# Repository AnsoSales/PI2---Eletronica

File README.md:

# PI2 - Eletrônica 

Repositório criado para armazenar os códigos utilizados para o microcontrolador principal do projeto de PI2 e para o arduino.

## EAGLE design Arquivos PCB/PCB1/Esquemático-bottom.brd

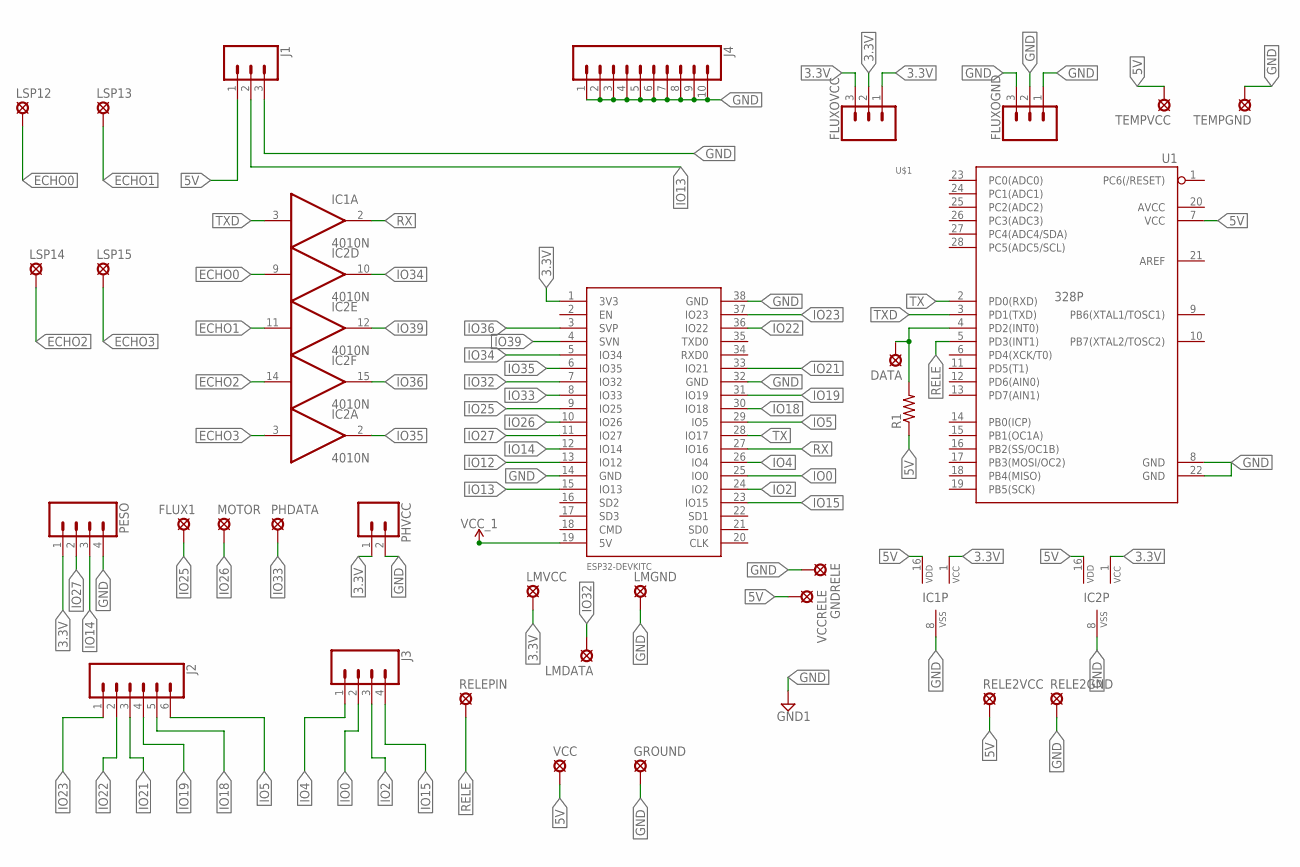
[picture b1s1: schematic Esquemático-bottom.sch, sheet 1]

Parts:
DATA: SE14
FLUX1: SE14
FLUXOGND: CONN_03; 1X03
FLUXOVCC: CONN_03; 1X03
GNDRELE: SE14
GROUND: SE14
IC1, IC2: 4010N; DIL16
J1: CONN_03; 1X03
J2: CONN_06SILK_FEMALE_PTH; 1X06
J3: CONN_04; 1X04
J4: CONN_10"; 1X10
LMDATA: SE14
LMGND: SE14
LMVCC: SE14
LSP12, LSP13, LSP14, LSP15: SE14
MOTOR: SE14
PESO: CONN_04; 1X04
PHDATA: SE14
PHVCC: CONN_02; 1X02
R1: R-US_0207/12; 0207/12
RELE2GND, RELE2VCC: SE14
RELEPIN: SE14
TEMPGND: SE14
TEMPVCC: SE14
U1: 328P; DIP28
U$1: ESP32DEVKITC; ESP32-DEVKITC
VCC: SE14
VCCRELE: SE14

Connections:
3.3V: FLUXOVCC.1, FLUXOVCC.2, FLUXOVCC.3, IC1.1 (VCC), IC2.1 (VCC), LMVCC.MP, PESO.1, PHVCC.1, U$1.1 (3V3)
5V: IC1.16 (VDD), IC2.16 (VDD), J1.1, R1.1, RELE2VCC.MP, TEMPVCC.MP, U1.7 (VCC), U$1.19 (5V), VCC.MP, VCCRELE.MP
ECHO0: IC2.9 (I), LSP12.MP
ECHO1: IC2.11 (I), LSP13.MP
ECHO2: IC2.14 (I), LSP14.MP
ECHO3: IC2.3 (I), LSP15.MP
GND: FLUXOGND.1, FLUXOGND.2, FLUXOGND.3, GNDRELE.MP, GROUND.MP, IC1.8 (VSS), IC2.8 (VSS), J1.3, J4.1, J4.2, J4.3, J4.4, J4.5, J4.6, J4.7, J4.8, J4.9, J4.10, LMGND.MP, PESO.4, PHVCC.2, RELE2GND.MP, TEMPGND.MP, U1.8 (GND), U1.22 (GND), U$1.14 (GND), U$1.32 (GND), U$1.38 (GND)
IO0: J3.2, U$1.25 (IO0)
IO2: J3.3, U$1.24 (IO2)
IO4: J3.1, U$1.26 (IO4)
IO5: J2.6, U$1.29 (IO5)
IO12: U$1.13 (IO12)
IO13: J1.2, U$1.15 (IO13)
IO14: PESO.3, U$1.12 (IO14)
IO15: J3.4, U$1.23 (IO15)
IO18: J2.5, U$1.30 (IO18)
IO19: J2.4, U$1.31 (IO19)
IO21: J2.3, U$1.33 (IO21)
IO22: J2.2, U$1.36 (IO22)
IO23: J2.1, U$1.37 (IO23)
IO25: FLUX1.MP, U$1.9 (IO25)
IO26: MOTOR.MP, U$1.10 (IO26)
IO27: PESO.2, U$1.11 (IO27)
IO32: LMDATA.MP, U$1.7 (IO32)
IO33: PHDATA.MP, U$1.8 (IO33)
IO34: IC2.10 (O), U$1.5 (IO34)
IO35: IC2.2 (O), U$1.6 (IO35)
IO36: IC2.15 (O), U$1.3 (SVP)
IO39: IC2.12 (O), U$1.4 (SVN)
unnamed: DATA.MP, R1.2, U1.4 (PD2(INT0))
RELE: RELEPIN.MP, U1.5 (PD3(INT1))
RX: IC1.2 (O), U$1.27 (IO16)
TX: U1.2 (PD0(RXD)), U$1.28 (IO17)
TXD: IC1.3 (I), U1.3 (PD1(TXD))

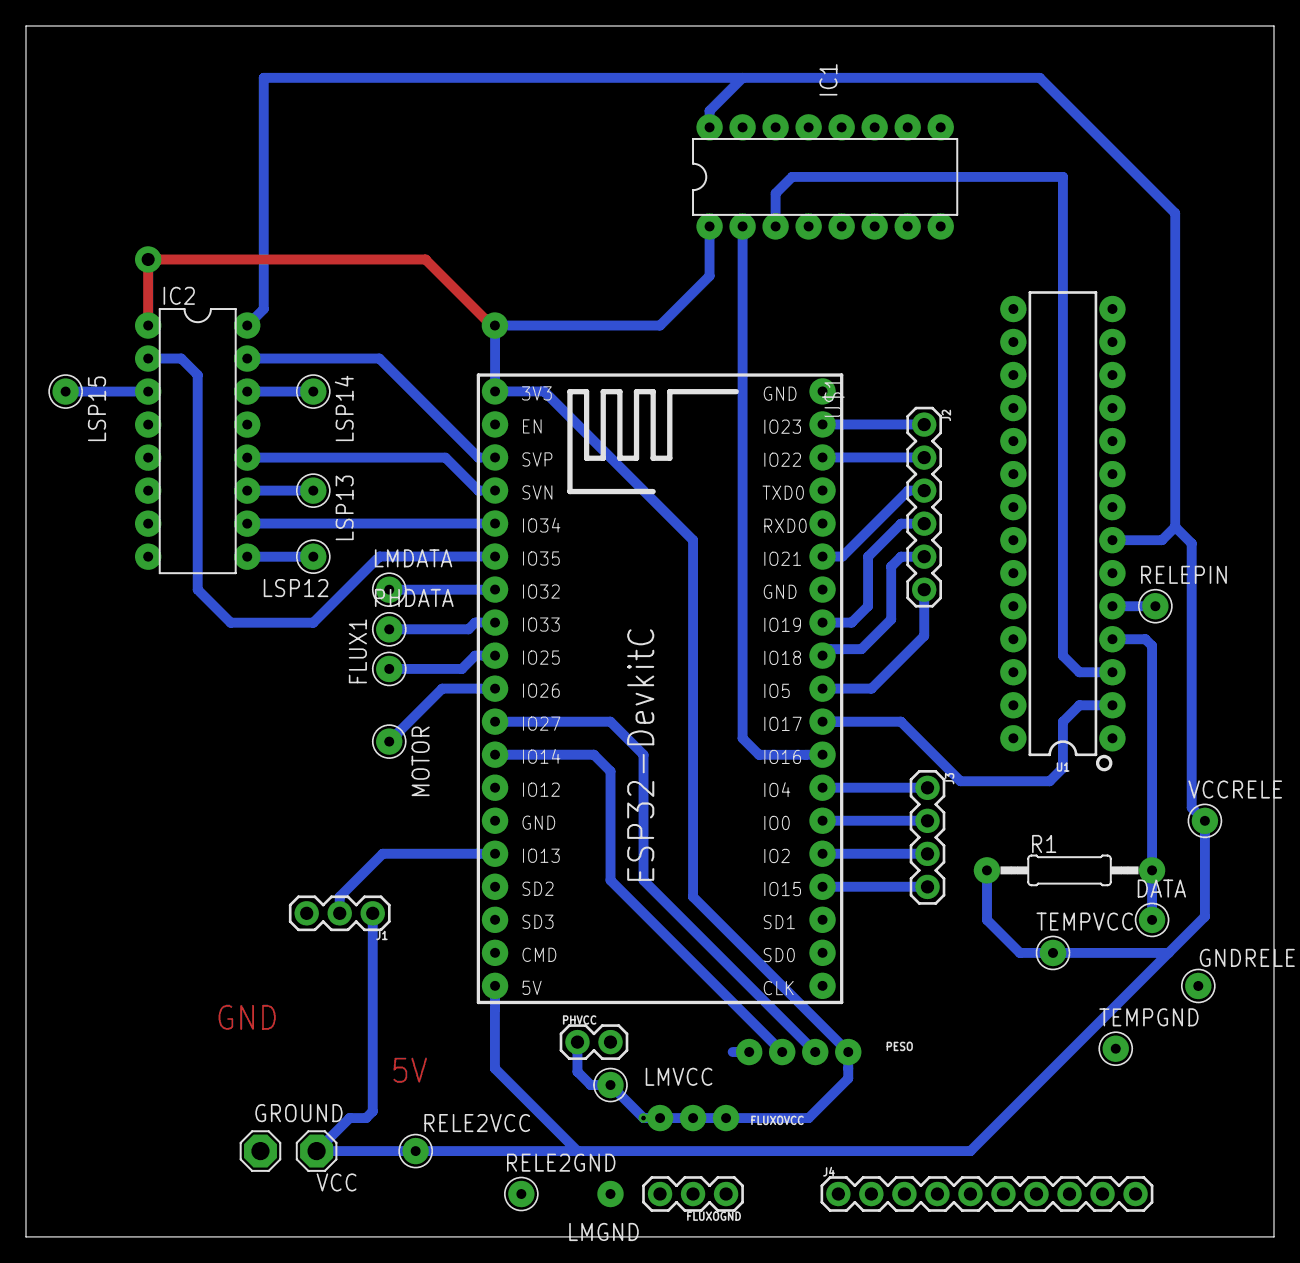
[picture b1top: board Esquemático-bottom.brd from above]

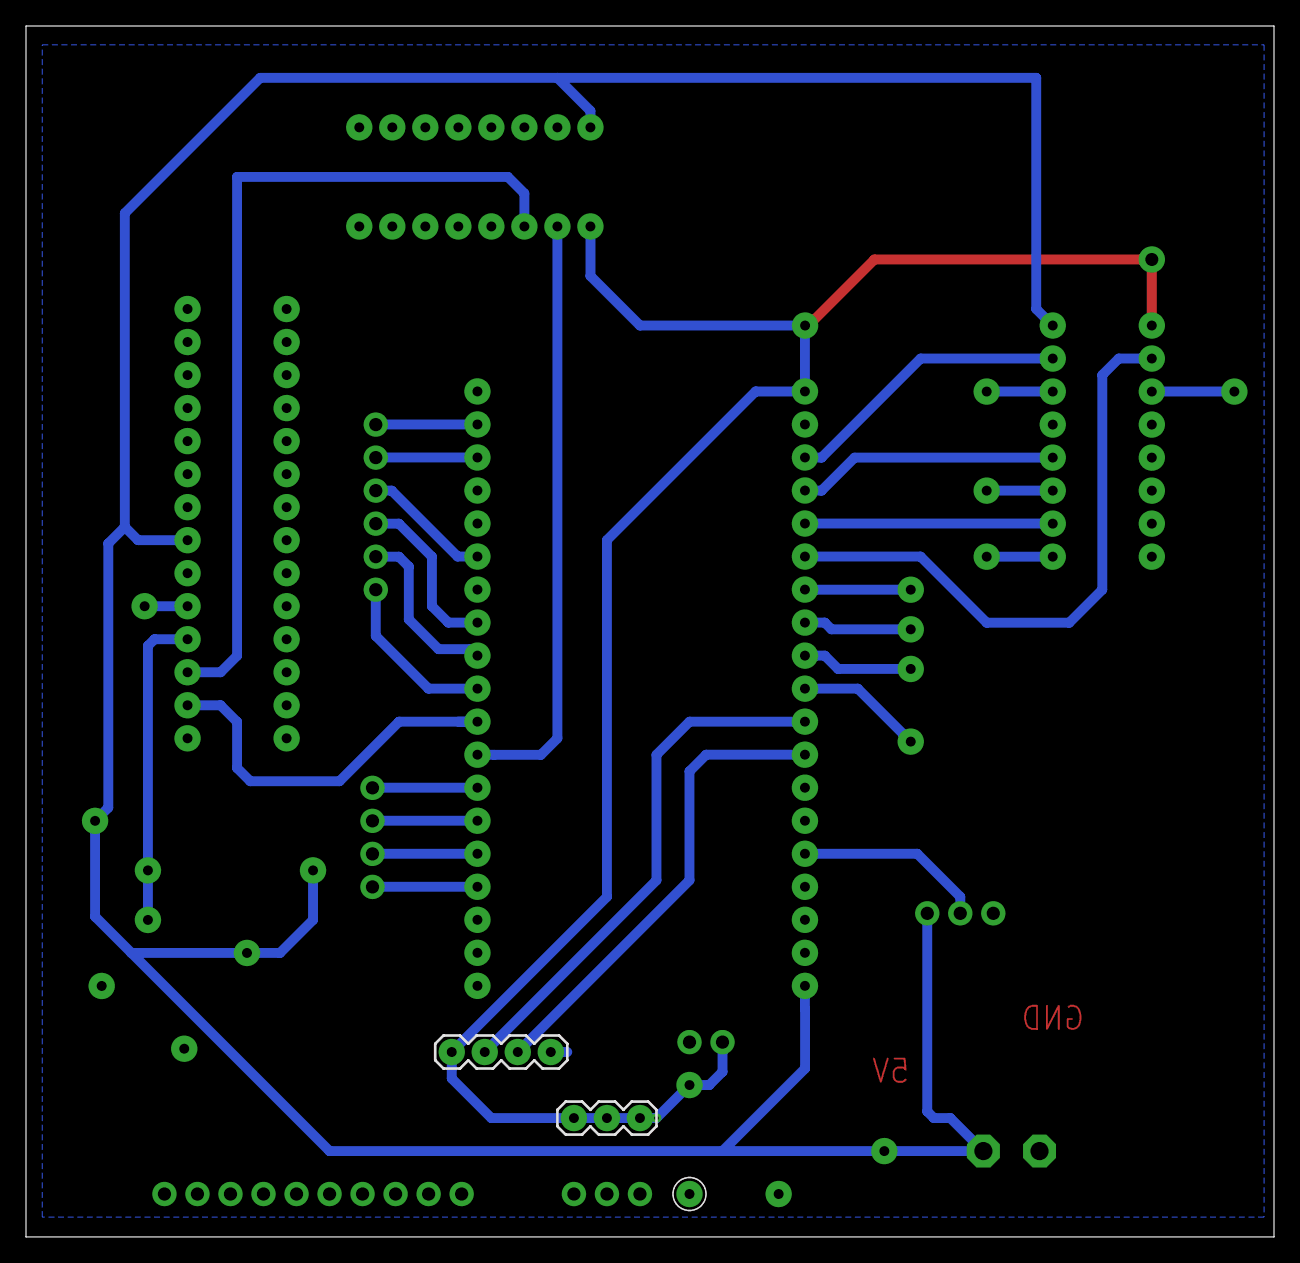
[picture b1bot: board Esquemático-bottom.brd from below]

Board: 2 copper layers, 96.0 x 93.1 mm, 33 parts (3 on the bottom side), 33 nets.

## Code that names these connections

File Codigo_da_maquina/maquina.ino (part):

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float vol_oleo=0,vol_etanol=0,massa_soda=0,agua_soda=0,vol_agua=0,agua_quente=0,vol_essencia1=0,vol_essencia2=0;


#define echo1 GPIO_NUM_36 //primeiro echo
#define echo2 GPIO_NUM_39 //segundo echo
#define echo3 GPIO_NUM_34 //terceiro echo
#define echo4 GPIO_NUM_35 //quarto echo
#define lmdata GPIO_NUM_32 //sensor de temperatura
#define phdata GPIO_NUM_33 //sensor de ph
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

//#define temp GPIO_NUM_26
//#define rele GPIO_NUM_4


#define Alcool  "2aaa9a64-6c81-4718-95eb-92fcdc1f95c8"
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
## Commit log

2019-05-11 Rename sensor_de_fluxo to sensor_de_fluxo.ino
2019-05-19 Create teste_duas_task.ino
    Código que ultiliza multitask. Ainda falta adicionar os outros sensores.
2019-06-08 Rename teste_duas_task.ino to main_maquina.ino
2019-06-20 Rename sensor_nivel_pote_2litros.txt to sensor_nivel_pote_2litros.ino
2019-06-20 Rename sensor_nivel_pote_1.5L.txt to sensor_nivel_pote_1.5L.ino
2019-06-20 Rename sensor_nivel_essencis.txt to sensor_nivel_essencis.ino

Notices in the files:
parts and their libraries:
SparkFun-PowerSymbols: Licensing: Creative Commons ShareAlike 4.0 International - https://creativecommons.org/licenses/by-sa/4.0
40xx-pad: Source: www.fairchildsemi.com CD4010.pdf  © 2000 Fairchild Semiconductor Corporation DS005945
